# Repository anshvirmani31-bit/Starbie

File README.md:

# Starbie

Starbie is a tiny motion-controlled digital pet: basically a desktop Tamagotchi with minimal gameplay buttons. Instead of pressing controls, you interact with it by physically moving the board.

## What it is

Starbie is designed to sit on your desk or stay in your hand. It reacts to how you handle (tilting it, moving it, shaking it, etc.)

## Why?

This project was for my week one Half-Life. It was the starter project given to us. I added my own touch to it by adding an on/off button. I thought that this could be useful since if you're connecting starbie to a battery back on the go, you may not want it to be constantly draining power, thus, the on/off button. This also changes my firmware. My firmware is different than the one that was given to us because I added the code for the third button. The code that I added changes the function of the third button. It allows it to control the flow of power from the starbie the the power source.

## How it works

This project includes a handful of parts such as a motion sensor/gyroscope, temperature and humidity sensor, etc. It uses the seeed studio XIAO ESP32-C3 as the brain. It also includes a 0.96 OLED screen for the menu and the firmware found in Starbie.ino allows you to use two of the three buttons to interact with the menu. The only other way to interact with Starbie is to shake it. Starbie takes advantage of the motion sensor to be able to tell when you shake it and it reacts accordingly. If you never interact with starbie it just sits on your desk slowly dying. Starbie also has stats from 0-100 being Joy, Energy, and Fullness. These can be increased or decreased from their starting value based on how you interact with starbie. Starbie is USB-C powered and doesn't have a built in battery meaning it needs to be plugges in to work and register inputs.

## Pictures

Finished PCB

Schematic

## BOM
| Item             | amount | cost USD (ea.) | Link                                                                  |
|------------------|--------|----------------|-----------------------------------------------------------------------|
| XIAO ESP32 C3    | 1      | 13.45          | https://www.seeedstudio.com/Seeed-XIAO-ESP32C3-p-5431.html            |
| 0.96 OLED        | 1      | 2.76           | https://www.aliexpress.com/item/1005006141235306.html                 |
| MPU6050          | 1      | 1.92           | https://www.amazon.ca/gp/product/B0GWX4N5N7?smid=AUV9BWKKX5AP0&th=1   |
| DHT11            | 1      | 3.73           | https://www.aliexpress.com/item/1005009668759587.html                 |
| MX Switches      | 1      | 2.01           | https://www.amazon.ca/gp/product/B0FQ5DDQYK?smid=A3HCNFR52IFXW0&psc=1 |
| Keycaps          | 1      | 1.25           | https://www.amazon.ca/gp/product/B0FX22HS4J?smid=A309HCDL4YKIK6&th=1  |
| 10k Resistor     | 1      | 1.21           | https://www.aliexpress.com/item/1005012176738771.html                 |
| PCB              | 1      | 3.50           | https://www.jlcpcb.com/                                               |
|                  |        |                |                                                                       |
| Total (each kit) | 1      | 30.28          |                                                                       |

## Repository Contents
- `BOM.csv` - Material costs including taxes and shipping
- `BOM.md` - Detailed material costs
- `JOURNAL.md` - Journal entries on what took how long
- `KiCad PCB.kicad_pcb` PCB file
- `KiCad PCB.kicad_sch` PCB schematic file
- `KiCad.PCB.zip` - Gerber and Drill files
- `Starbie.ino` - Firmware/code

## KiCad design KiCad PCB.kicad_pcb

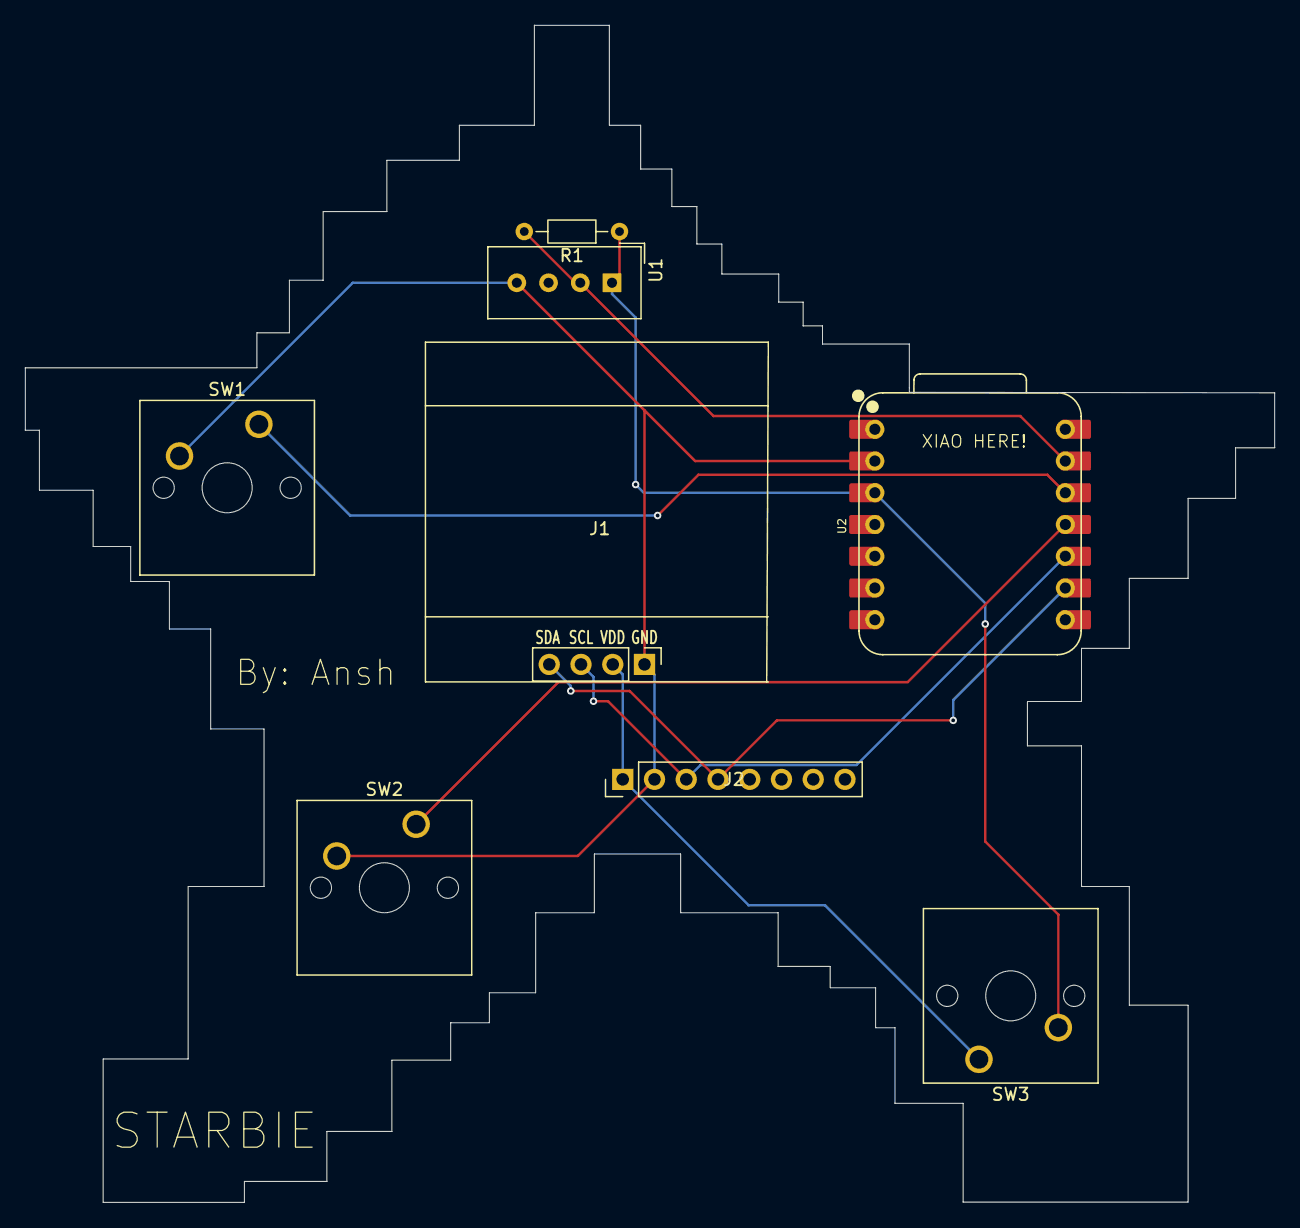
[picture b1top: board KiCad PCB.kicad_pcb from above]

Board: 2 copper layers, 100.0 x 94.2 mm, 8 parts (0 on the bottom side), 8 nets.

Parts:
J1: Conn_01x04_Pin; Display_128x64_096_I2C
J2: Conn_01x08_Pin; PinHeader_1x08_P2.54mm_Vertical
R1: 10k; R_Axial_DIN0204_L3.6mm_D1.6mm_P7.62mm_Horizontal
SW1, SW2, SW3: SW_Push; SW_Cherry_MX_1.00u_PCB
U1: DHT11; Aosong_DHT11_5.5x12.0_P2.54mm
U2: XIAO-ESP32-C3-SMD; XIAO-ESP32-C6-DIP

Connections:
+3.3V: R1.1, SW3.2, U1.1 (VDD), U2.3 (D2)
/DHT11 DATA: R1.2, U1.2 (DATA), U2.13 (GND)
/GPIO2: SW1.1, U2.12 (3V3_OUT)
/GPIO3: SW2.1, U2.11 (D10)
/SCL: J1.3, J2.3, U2.10 (D9/BOOT)
/SDA: J1.4, J2.4, U2.9 (D8)
/VCC_RAW: J1.2, J2.1, SW3.1
GND: J1.1, J2.2, SW1.2, SW2.2, U1.4 (GND), U2.2 (D1)
